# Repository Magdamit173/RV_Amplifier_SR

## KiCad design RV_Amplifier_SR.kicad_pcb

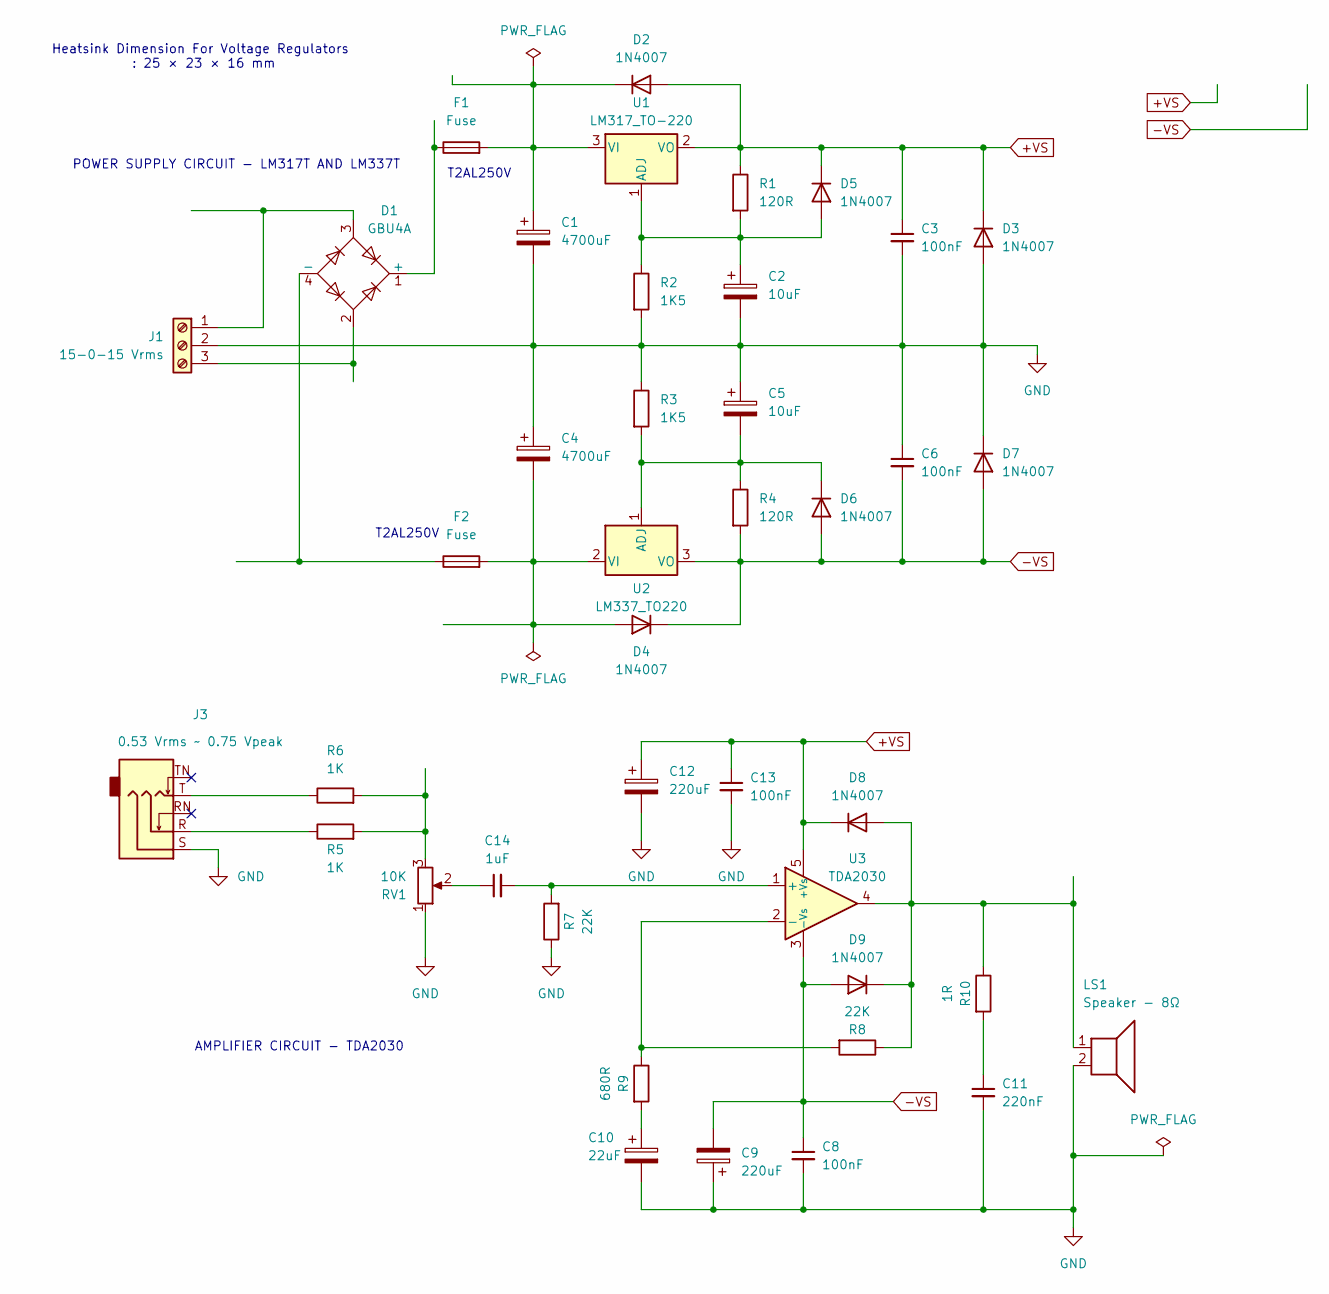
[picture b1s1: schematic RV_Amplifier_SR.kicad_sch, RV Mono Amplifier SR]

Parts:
C1, C4: 4700uF; CP_Radial_D25.0mm_P10.00mm_SnapIn
C2, C5: 10uF; CP_Radial_D5.0mm_P2.50mm
C3, C6, C8, C13: 100nF; C_Disc_D5.0mm_W2.5mm_P2.50mm
C9, C12: 220uF; CP_Radial_D10.0mm_P5.00mm
C10: 22uF; CP_Radial_D5.0mm_P2.50mm
C11: 220nF; C_Disc_D5.0mm_W2.5mm_P2.50mm
C14: 1uF; C_Disc_D5.0mm_W2.5mm_P2.50mm
D1: GBU4A; Diode_Bridge_Vishay_GBU
D2, D3, D4, D5, D6, D7, D8, D9: 1N4007; D_DO-41_SOD81_P10.16mm_Horizontal
F1, F2: Fuse; Fuseholder_Cylinder-5x20mm_Schurter_0031_8201_Horizontal_Op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
J1: 15-0-15 Vrms; TerminalBlock_Phoenix_MKDS-1,5-3_1x03_P5.00mm_Horizontal
J3: 0.53 Vrms ~ 0.75 Vpeak; Jack_3.5mm_CUI_SJ1-3525N_Horizontal
LS1: Speaker - 8Ω; TerminalBlock_Phoenix_MKDS-1,5-2_1x02_P5.00mm_Horizontal
R1, R4: 120R; R_Axial_DIN0309_L9.0mm_D3.2mm_P15.24mm_Horizontal
R2, R3: 1K5; R_Axial_DIN0207_L6.3mm_D2.5mm_P10.16mm_Horizontal
R5, R6: 1K; R_Axial_DIN0207_L6.3mm_D2.5mm_P10.16mm_Horizontal
R7, R8: 22K; R_Axial_DIN0207_L6.3mm_D2.5mm_P10.16mm_Horizontal
R9: 680R; R_Axial_DIN0207_L6.3mm_D2.5mm_P10.16mm_Horizontal
R10: 1R; R_Axial_DIN0516_L15.5mm_D5.0mm_P25.40mm_Horizontal
RV1: 10K; TerminalBlock_Phoenix_MKDS-1,5-3_1x03_P5.00mm_Horizontal
U1: LM317_TO-220; TO-220-3_Vertical
U2: LM337_TO220; TO-220-3_Vertical
U3: TDA2030; TO-220-5_P3.4x3.7mm_StaggerOdd_Lead3.8mm_Vertical

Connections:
+VS: C3.1, C12.1, C13.1, D2.2 (A), D3.1 (K), D5.1 (K), D8.1 (K), R1.1, U1.2 (VO), U3.5 (+Vs)
-VS: C6.2, C8.1, C9.2, D4.1 (K), D6.2 (A), D7.2 (A), D9.2 (A), R4.2, U2.3 (VO), U3.3 (-Vs)
GND: C1.2, C2.2, C3.2, C4.1, C5.1, C6.1, C8.2, C9.1, C10.2, C11.2, C12.2, C13.2, D3.2 (A), D7.1 (K), J1.2, J3.S, LS1.2, R2.2, R3.1, R7.1, RV1.1
unnamed: C10.1, R9.2
unnamed: C11.1, R10.2
unnamed: C14.1, RV1.2
unnamed: D1.1 (+), F1.1
unnamed: D1.4 (-), F2.1
unnamed: C1.1, D2.1 (K), F1.2, U1.3 (VI)
unnamed: C4.2, D4.2 (A), F2.2, U2.2 (VI)
unnamed: C2.1, D5.2 (A), R1.2, R2.1, U1.1 (ADJ)
unnamed: C5.2, D6.1 (K), R3.2, R4.1, U2.1 (ADJ)
unnamed: D8.2 (A), D9.1 (K), LS1.1, R8.1, R10.1, U3.4
unnamed: D1.3, J1.1
unnamed: D1.2, J1.3
unnamed: J3.R, R5.1
unnamed: J3.T, R6.1
unnamed: R5.2, R6.2, RV1.3
unnamed: C14.2, R7.2, U3.1 (+)
unnamed: R8.2, R9.1, U3.2 (-)

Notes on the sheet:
AMPLIFIER CIRCUIT - TDA2030
T2AL250V
POWER SUPPLY CIRCUIT - LM317T AND LM337T
Heatsink Dimension For Voltage Regulators : 25 × 23 × 16 mm

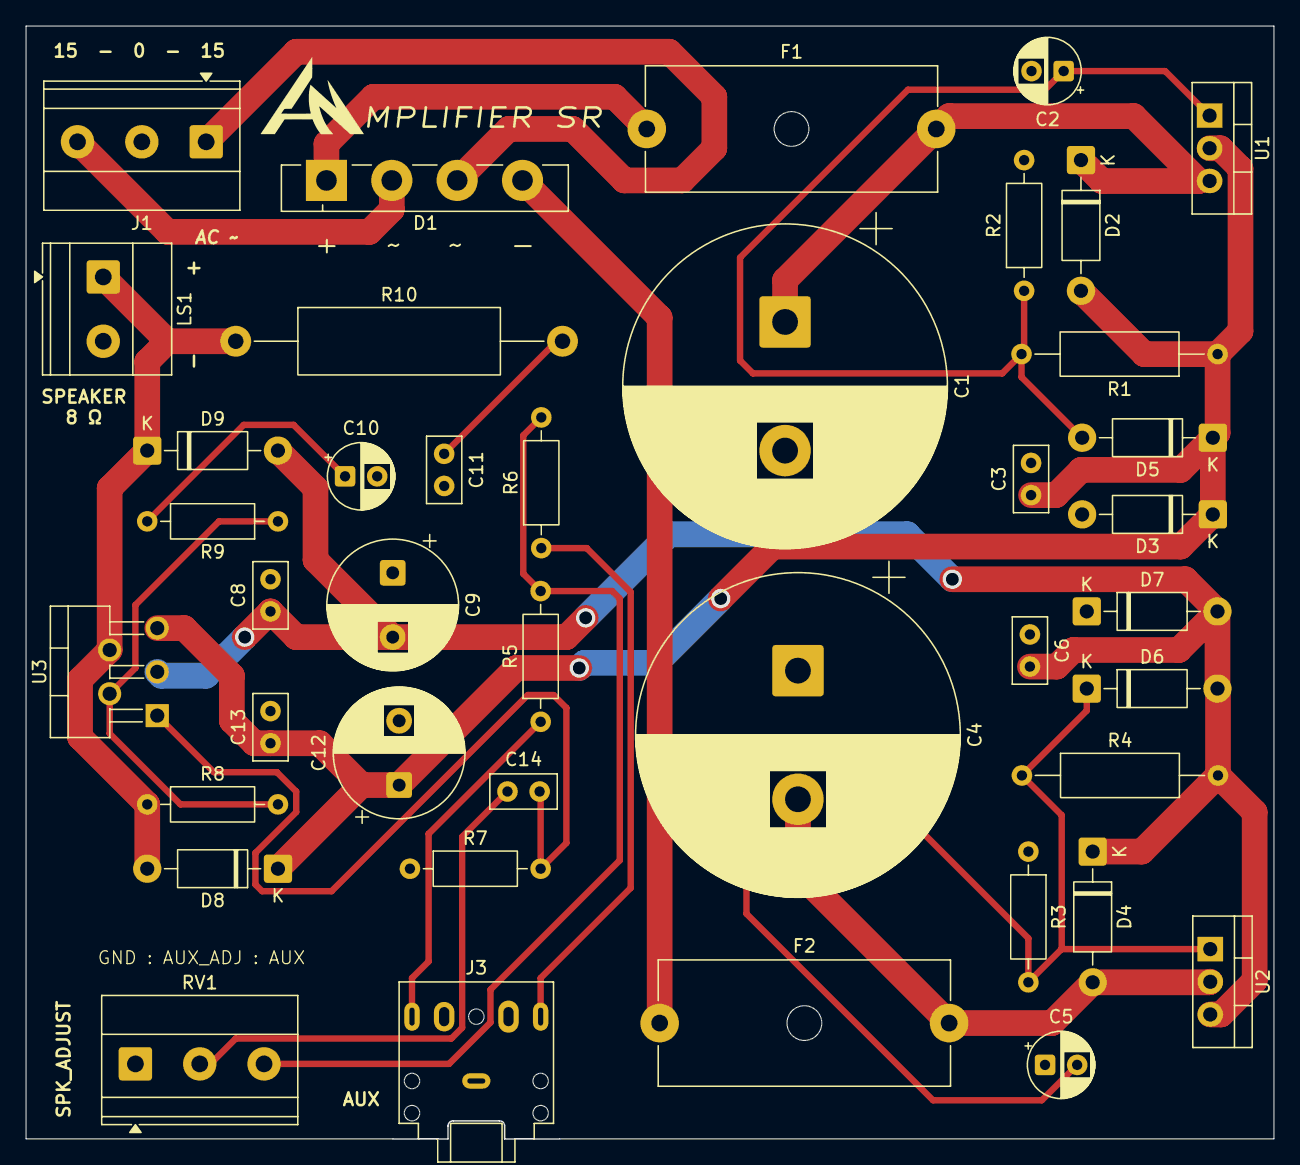
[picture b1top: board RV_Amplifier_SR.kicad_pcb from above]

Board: 2 copper layers, 97.0 x 86.5 mm, 41 parts (0 on the bottom side), 20 nets.

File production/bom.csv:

Designator,Footprint,Quantity,Value,LCSC Part #
"C1, C4",CP_Radial_D25.0mm_P10.00mm_SnapIn,2,4700uF,
C10,CP_Radial_D5.0mm_P2.50mm,1,22uF,
C11,C_Disc_D5.0mm_W2.5mm_P2.50mm,1,220nF,
"C12, C9",CP_Radial_D10.0mm_P5.00mm,2,220uF,
"C13, C3, C6, C8",C_Disc_D5.0mm_W2.5mm_P2.50mm,4,100nF,
C14,C_Disc_D5.0mm_W2.5mm_P2.50mm,1,1uF,
"C2, C5",CP_Radial_D5.0mm_P2.50mm,2,10uF,
D1,Diode_Bridge_Vishay_GBU,1,GBU4A,
"D2, D3, D4, D5, D6, D7, D8, D9",D_DO-41_SOD81_P10.16mm_Horizontal,8,1N4007,
"F1, F2",Fuseholder_Cylinder-5x20mm_Schurter_0031_8201_Horizontal_Open,2,Fuse,
J1,"TerminalBlock_Phoenix_MKDS-1,5-3_1x03_P5.00mm_Horizontal",1,15-0-15 Vrms,
J3,Jack_3.5mm_CUI_SJ1-3525N_Horizontal,1,0.53 Vrms ~ 0.75 Vpeak,
LS1,"TerminalBlock_Phoenix_MKDS-1,5-2_1x02_P5.00mm_Horizontal",1,Speaker - 8Ω,
"R1, R4",R_Axial_DIN0309_L9.0mm_D3.2mm_P15.24mm_Horizontal,2,120R,
R10,R_Axial_DIN0516_L15.5mm_D5.0mm_P25.40mm_Horizontal,1,1R,
"R2, R3",R_Axial_DIN0207_L6.3mm_D2.5mm_P10.16mm_Horizontal,2,1K5,
"R5, R6",R_Axial_DIN0207_L6.3mm_D2.5mm_P10.16mm_Horizontal,2,1K,
"R7, R8",R_Axial_DIN0207_L6.3mm_D2.5mm_P10.16mm_Horizontal,2,22K,
R9,R_Axial_DIN0207_L6.3mm_D2.5mm_P10.16mm_Horizontal,1,680R,
RV1,"TerminalBlock_Phoenix_MKDS-1,5-3_1x03_P5.00mm_Horizontal",1,10K,
U1,TO-220-3_Vertical,1,LM317_TO-220,
U2,TO-220-3_Vertical,1,LM337_TO220,
U3,TO-220-5_P3.4x3.7mm_StaggerOdd_Lead3.8mm_Vertical,1,TDA2030,
